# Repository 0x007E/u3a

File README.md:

# `U3A` - USB/UART/UPDI - Adapter

The `U3A` project is based on a ([FT232](#additional-information)) that ist used as USB (Full Speed) to serial UART transceiver. Most signals of the ([FT232](#additional-information)) are routed to the connector pins `J2` and `J4`. Whithin the DIP switches the adapter can be switched from `UART` to `UPDI` mode to program microcontrollers. It is possible to select between two voltage sources. Either `5V` from USB or `3V3` from the internal LDO on the board.

> The LDO itself can drive around `800 mA`. Therefore it is necessary to install a cooling unit inside the housing. The mount for this is already provided in the housing.

| Experience | Level |
|:------------|:-----:|
| Soldering   |  |
| Mechanical  |  |

# Adapter-Boards

| RS232 | RS422 | RS485 |
|:---------:|:----------:|:-----:|
|  |  |  |
| Schematic | Schematic | Schematic |
| [pdf](https://github.com/0x007E/u3a_rs232/releases/latest/download/schematic.pdf) / [cadlab](https://cadlab.io/project/29701/main/files) | [pdf](https://github.com/0x007E/u3a_rs422/releases/latest/download/schematic.pdf) / [cadlab](https://cadlab.io/project/29767/main/files) | [pdf](https://github.com/0x007E/u3a_rs485/releases/latest/download/schematic.pdf) / [cadlab](https://cadlab.io/project/29763/main/files) |
| [GitHub](https://github.com/0x007e/u3a_rs232) | [GitHub](https://github.com/0x007e/u3a_rs422) | [GitHub](https://github.com/0x007e/u3a_rs485) |

# Downloads

| Type      | File               | Description              |
|:---------:|:------------------:|:-------------------------|
| Schematic | [pdf](https://github.com/0x007E/u3a/releases/latest/download/schematic.pdf) / [cadlab](https://cadlab.io/project/29697/main/files) | Schematic files |
| Board | [pdf](https://github.com/0x007E/u3a/releases/latest/download/pcb.pdf) / [cadlab](https://cadlab.io/project/29697/main/files) | Board file |
| Drill | [pdf](https://github.com/0x007E/u3a/releases/latest/download/drill.pdf) | Drill file |
| BoM | [xlsx](https://github.com/0x007E/u3a/releases/latest/download/bom.xlsx) / [html](https://github.com/0x007E/u3a/releases/latest/download/ibom.html)          | Bill of Material as Excel/interactive HTML |
| PCB    | [zip](https://github.com/0x007E/u3a/releases/latest/download/kicad.zip) / [tar](https://github.com/0x007E/u3a/releases/latest/download/kicad.tar.gz)    | KiCAD/Gerber/BoM/Drill files       |
| Mechanical | [zip](https://github.com/0x007E/u3a/releases/latest/download/freecad.zip) / [tar](https://github.com/0x007E/u3a/releases/latest/download/freecad.tar.gz) | FreeCAD/Housing and PCB (STEP/STL) files     |

# Hardware

There are two parts of the hardware. The pcb and the housing of the `U3A`. The pcb is created with [KiCAD](#additional-information) and the housing with `FreeCAD`. All files are built with `github actions` so that they are ready for a production environment. The housing is printed with a 3D-printer (`Dremel 3D40`).

## PCB

The circuit board is populated on both sides (Top, Bottom). The best way for soldering the `SMD` components is within a vapor phase soldering system and for the `THT` components with a standard soldering system.

### Top Layer

### Bottom Layer

## Mechanical

The housing has a tolerance of `0.2mm` on each side of the case. So the pcb should fit perfectly in the housing. The tolerance can be modified with `FreeCAD` in the `Parameter` Spreadsheet.

### Assembled

### Exploded

# Connection/Setup

The `U3A` is powerd over USB with `5V`. The voltage of the pins can be setup through jumper `J1`. Either `5V` or `3V3`. The output of the system is driven by `CBUS4`. It needs to be configured through [FT_PROG](#additional-information). Mostly pins of the IC are routed to the connectors `J2` and `J4`

| CBUS | Value         | Description                                       |
|:----:|:--------------|:--------------------------------------------------|
| 0    | TXLED#        | Transmit signal LED pin                           |
| 1    | RXLED#        | Receive signal LED pin                            |
| 2    | TXDEN/SLEEP#  | Depends on external module (`u3a_rs422`/`_rs485`) |
| 3    | PWREN#        | Drive external hardware (`u3a_rs422`/`_rs485`)    |
| 4    | PWREN#        | Drive external `VCC` pins with selected voltage   |

## Simple loopback setup for testing purpose

``` bash
#
#               +-----------------------------------+      +---------------------+
#               |J2     U                       +---+---+  |                     |
#            +--+--+    S                       |  USB  |--+ +-----------------+ |
#            | VCC |    B      UPDI             +---+---+  | | TeraTerm        | |
#            | GND |    /    +---+---+              |      | | ~~~~~~~~        | |
#            | PDI |    U    |   |   |              |      | | ~~~~~           | |
#            | CTS |    A    |   |   |              |      | | ~~~~~~~~~~~~    | |
#      L     | RTS |    R    | X | X |              |      | |                 | |
#      O +---+ TXD |    T    +---+---+     +-+      |      | +-----------------+ |
#      O +---+ RXD |    /                 / /       |      |                     |
#      P     +-----+    U               +-+-+-+-+-+-+      | Computer            |
#      B        |       P               | 5V  | 3V3 |      |                     |
#      A        |       D               +-----+-----+      +---------------------+
#      C        |  J4   I                           |
#      K        | +---+---+---+---+---+---+---+---+ |
#               | | V | C | C | D | D | D | R | G | |
#               +-+ C | B | B | C | T | C | I | N +-+
#                 | C | 3 | 2 | D | R | R |   | D |
#                 +---+---+---+---+---+---+---+---+
```

# Errata/Errors

On some `FT232RL` (NRND) a usb-connection issue occurs if the volatge jumper (`J1`) is set to `3V3`. To solve this issue remove jumper `J1` before the usb-port is connected to a computer and reinsert the jumper `J1` after the connection between the computer and `FT232` is initiated. Details can be found [here](https://github.com/0x007E/u3a/issues/1).

# Additional Information

| Type       | Link                                                                 | Description                                          |
|:----------:|:--------------------------------------------------------------------:|:-----------------------------------------------------|
| FT232R     | [pdf](https://ftdichip.com/wp-content/uploads/2020/08/DS_FT232R.pdf) | USB to serial UART interface IC                      |
| FT_PROG    | [web](https://ftdichip.com/utilities/#ft_prog)                       | EEPROM programming utility for use with FTDI devices |
| KiCAD      | [web](https://www.kicad.org/)                                        | KiCAD project page                                   |
| FreeCAD    | [web](https://www.freecad.org/)                                      | FreeCAD project page                                 |

---

R. GAECHTER

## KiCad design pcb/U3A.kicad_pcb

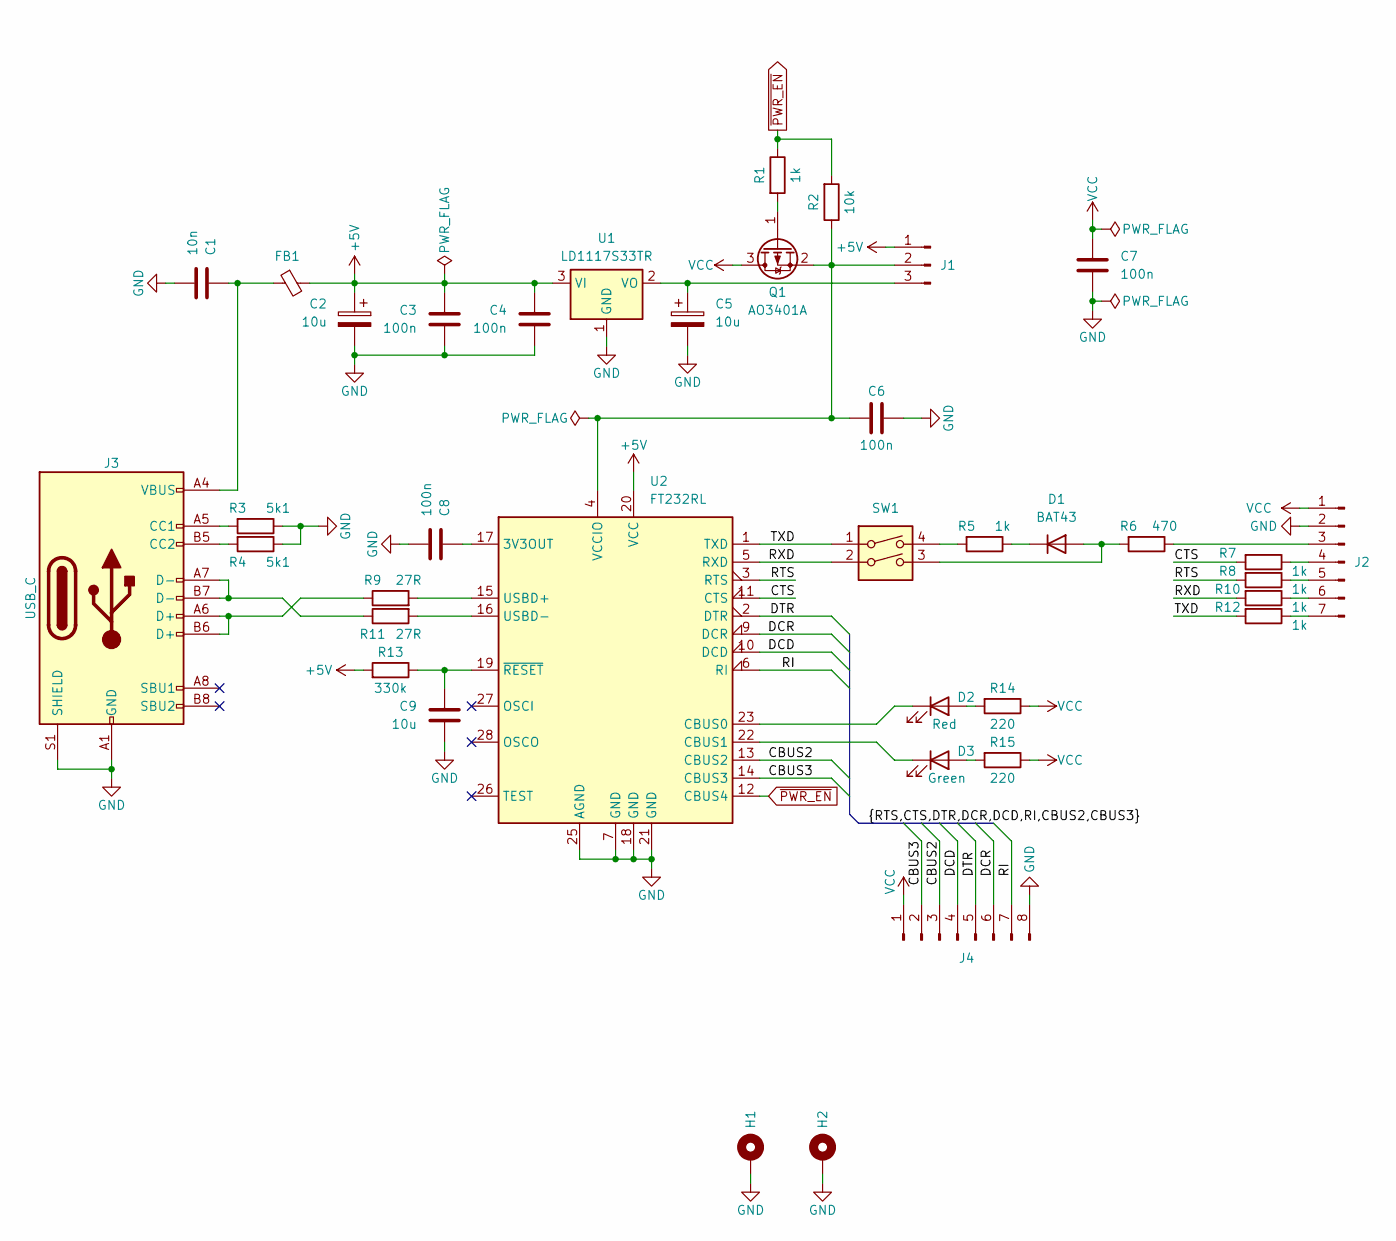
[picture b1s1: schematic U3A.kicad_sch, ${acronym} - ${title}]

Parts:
C1: 10n; C_1206_3216Metric
C2, C5: 10u; CP_EIA-6032-28_Kemet-C
C3, C4, C6, C7, C8: 100n; C_1206_3216Metric
C9: 10u; C_1206_3216Metric
D1: BAT43; D_MiniMELF
D2: Red; LED_1206_3216Metric
D3: Green; LED_1206_3216Metric
FB1: FerriteBead_Small; L_1206_3216Metric
H1, H2: MountingHole_Pad; MountingHole_2.7mm_M2.5_Pad
J1: Conn_01x03_Pin; PinHeader_1x03_P2.54mm_Vertical
J2: Conn_01x07_Pin; PinHeader_1x07_P2.54mm_Vertical
J3: USB_C; USB_C_Receptacle_GCT_USB4110
J4: Conn_01x08_Pin; PinHeader_1x08_P2.54mm_Vertical
Q1: AO3401A; SOT-23
R1, R5, R7, R8, R10, R12: 1k; R_1206_3216Metric
R2: 10k; R_1206_3216Metric
R3, R4: 5k1; R_1206_3216Metric
R6: 470; R_1206_3216Metric
R9, R11: 27R; R_1206_3216Metric
R13: 330k; R_1206_3216Metric
R14, R15: 220; R_1206_3216Metric
SW1: SW_DIP_x02; SW_DIP_SPSTx02_Slide_6.7x6.64mm_W8.61mm_P2.54mm_LowProfile
U1: LD1117S33TR; TO-252-3_TabPin2
U2: FT232RL; SSOP-28_5.3x10.2mm_P0.65mm

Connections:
+5V: C2.1, C3.2, C4.2, FB1.2, J1.1, R13.2, U1.3 (VI), U2.20 (VCC)
/CBUS2: J4.3, U2.13 (CBUS2)
/CBUS3: J4.2, U2.14 (CBUS3)
/CTS: R7.2, U2.11 (CTS)
/DCD: J4.4, U2.10 (DCD)
/DCR: J4.6, U2.9 (DCR)
/DTR: J4.5, U2.2 (DTR)
/RI: J4.7, U2.6 (RI)
/RTS: R8.2, U2.3 (RTS)
/RXD: R10.2, SW1.2, U2.5 (RXD)
/TXD: R12.2, SW1.1, U2.1 (TXD)
GND: C1.1, C2.2, C3.1, C4.1, C5.2, C6.1, C7.1, C8.1, C9.1, H1.1, H2.1, J2.2, J3.A1 (GND), J3.A12 (GND), J3.B1 (GND), J3.B12 (GND), J3.S1 (SHIELD), J4.8, R3.1, R4.1, U1.1 (GND), U2.7 (GND), U2.18 (GND), U2.21 (GND), U2.25 (AGND)
unnamed: C1.2, FB1.1, J3.A4 (VBUS), J3.A9 (VBUS), J3.B4 (VBUS), J3.B9 (VBUS)
unnamed: D1.2 (A), R6.2, SW1.3
unnamed: D1.1 (K), R5.1
unnamed: D2.2 (A), R14.2
unnamed: D2.1 (K), U2.23 (CBUS0)
unnamed: D3.2 (A), R15.2
unnamed: D3.1 (K), U2.22 (CBUS1)
unnamed: C6.2, J1.2, Q1.2 (S), R2.1, U2.4 (VCCIO)
unnamed: C5.1, J1.3, U1.2 (VO)
unnamed: J2.3, R6.1
unnamed: J2.4, R7.1
unnamed: J2.5, R8.1
unnamed: J2.6, R10.1
unnamed: J2.7, R12.1
unnamed: J3.A5 (CC1), R3.2
unnamed: J3.B5 (CC2), R4.2
unnamed: J3.A6 (D+), J3.B6 (D+), R9.1
unnamed: J3.A7 (D-), J3.B7 (D-), R11.1
unnamed: Q1.1 (G), R1.2
unnamed: R5.2, SW1.4
unnamed: C8.2, U2.17 (3V3OUT)
unnamed: R9.2, U2.15 (USBD+)
unnamed: R11.2, U2.16 (USBD-)
unnamed: C9.2, R13.1, U2.19 (~RESET)
VCC: C7.2, J2.1, J4.1, Q1.3 (D), R14.1, R15.1
~PWR_EN: R1.1, R2.2, U2.12 (CBUS4)

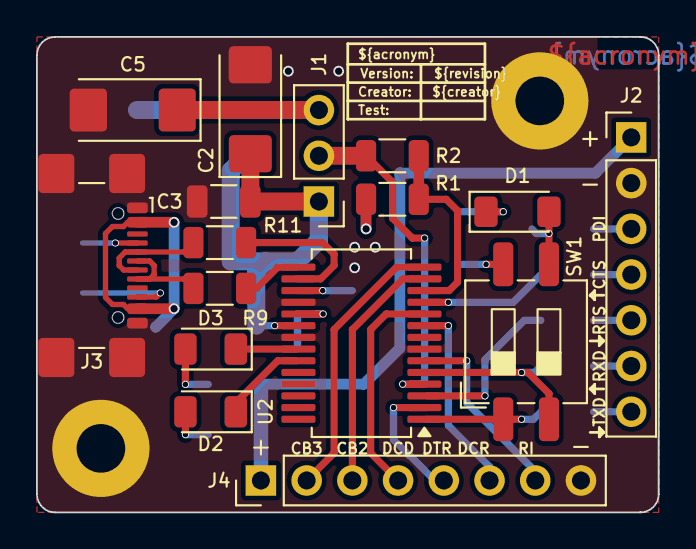
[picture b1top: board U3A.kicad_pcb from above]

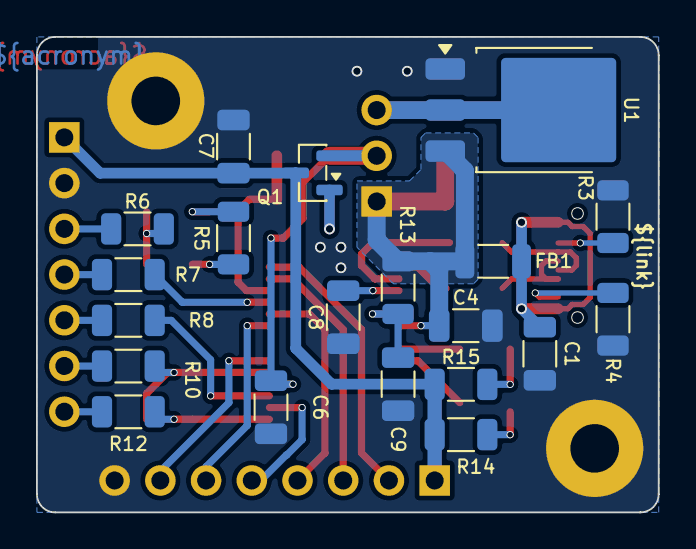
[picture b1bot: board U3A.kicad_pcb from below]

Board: 2 copper layers, 34.5 x 26.4 mm, 38 parts (20 on the bottom side), 38 nets.

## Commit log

2025-10-19 Add README.md
2025-10-19 Add build pipeline
2025-10-19 Add release pipeline
2025-10-20 Remove unused symbol library
2025-10-20 Change connector name
2025-11-06 Fix wrong vendor-id of device
2025-11-13 Fix voltage error on startup
2025-11-25 Add deepwiki badge
2025-12-22 Optimize bottom fabrication layer
2026-01-09 close #1; Add errata/error section
2026-01-09 Link usb-connection issue
2026-01-09 Fix section typo
2026-01-09 Change name of FT232 IC
2026-01-09 Add CBUS pin description
2026-06-20 Update to KiCAD 9
2026-06-20 Rename/Add/Remove bom fields
2026-06-20 Update build pipeline
2026-06-20 Update release pipeline
2026-06-20 Fix incorrect adapter schematic links
2026-06-21 Adapt output filenames
2026-06-21 Add missing values in bom
2026-06-21 Adapt config and update action versions
2026-06-21 Fix wrong kibot config file
2026-06-22 Fix freecad path issue
2026-06-22 Fix thumbnail image reference

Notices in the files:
README.md:
License CC By-NC-SA
parts and their libraries:
license: CC BY-NC-SA 4.0
